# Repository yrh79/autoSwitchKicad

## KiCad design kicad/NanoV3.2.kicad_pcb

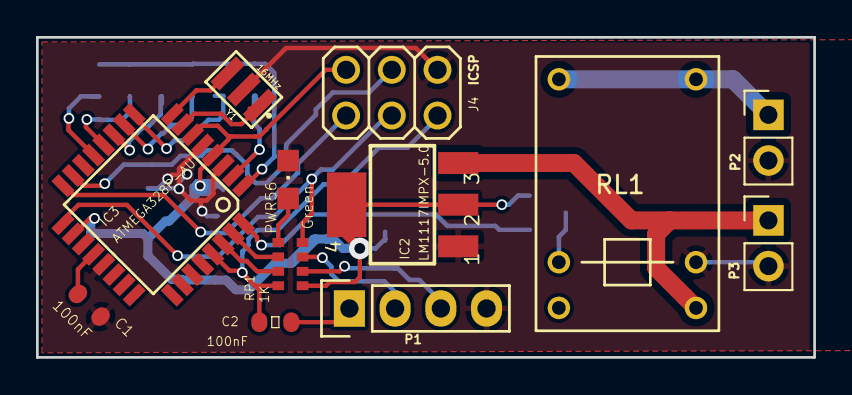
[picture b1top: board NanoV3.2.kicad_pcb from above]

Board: 2 copper layers, 43.2 x 17.8 mm, 24 parts (0 on the bottom side), 26 nets.

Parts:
C1, C2: 100nF; C0603-ROUND
C3, C7, C8: 1uF; C0603-ROUND
C5: 4,7uF_16V; TAN-A
FRAME1: DNP; FRAME
IC2: LM1117IMPX-5.0; LINEAR_SOT223
IC3: ATMEGA328P-AU; TQFP32-08
J4: 2X03
JP1, JP2, JP3, JP4, JP5, JP6: SMD-Jummper
P1: TTL; Pin_Header_Straight_1x04
P2: OUT; Pin_Header_Straight_1x02_Pitch2.54mm
P3: INPUT; Pin_Header_Straight_1x02_Pitch2.54mm
PWR56: Green; CHIPLED_0805
Q1: SS8050; SOT-23
RL1: Relay_HK4100F
RP1: 1K; CAY16
Y1: 16MHz; Crystal3215

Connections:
+5V: C3.1, C5.1, C7.1, C8.1, IC2.2, IC2.4, IC3.4, IC3.6, IC3.18, J4.2, Q1.2, RP1.5
/AREF: C1.1, IC3.20
/D0/RX: IC3.30, RP1.3
/D1/TX: IC3.31, RP1.2
/D2: IC3.32, Q1.1
/D3: IC3.1, JP1.2, JP2.2, JP3.2, JP4.2, JP5.2, JP6.2
/D4: IC3.2, JP1.1
/D5: IC3.9, JP2.1
/D6: IC3.10, JP3.1
/D7: IC3.11, JP4.1
/D8: IC3.12, JP5.1
/D9: IC3.13, JP6.1
/D11/MOSI: IC3.15, J4.4
/D12/MISO: IC3.16, J4.1
/D13/SCK: IC3.17, J4.3, RP1.8
/N$1: IC3.8, Y1.3
/N$2: IC3.7, Y1.1
/N$3: PWR56.A, RP1.1
/RESET: C2.1, IC3.29, J4.5, RP1.4
/RX: P1.3, RP1.6
/TX: P1.2, RP1.7
COM: C1.2, C3.2, C5.2, C7.2, C8.2, IC2.1, IC3.3, IC3.5, IC3.21, J4.6, P1.4, P2.2, P3.2, PWR56.C, RL1.A2, Y1.2
unnamed: C2.2, P1.1
unnamed: P2.1, RL1.10, RL1.11
unnamed: Q1.3, RL1.A1
VIN: IC2.3, P3.1, RL1.14

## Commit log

2017-12-19 deleted un-used files, added .gitignore
2017-12-19 modified arduino nano schematic to delete USB stuffs - further works needed
2017-12-19 updated schematic, not workable yet
2017-12-20 minor update
2017-12-21 added relay
2017-12-21 updated libs and deleted reset button
2017-12-21 moved some components to back
2017-12-21 moved components to right position and clean up marks
2017-12-22 finished layout
2017-12-22 updated jumpper pad
2017-12-22 Version V0.9
2017-12-22 Version 0.9
2017-12-22 removed outputs dir
2017-12-22 updated RP1 network and crytal footprint
2017-12-23 updated Q1 footprint and updated routing
2017-12-23 minor update of routing
2017-12-24 update of routing to move the 4.7uf under the CPU
2017-12-24 added document for relay
2017-12-25 make the input of regulator thicker
2017-12-25 make the input of regulator more reasonable
2017-12-26 aligned the jumppers
2017-12-28 fixed a footprint error for HK4001 relay
2017-12-29 fixed a bug with the transistor
